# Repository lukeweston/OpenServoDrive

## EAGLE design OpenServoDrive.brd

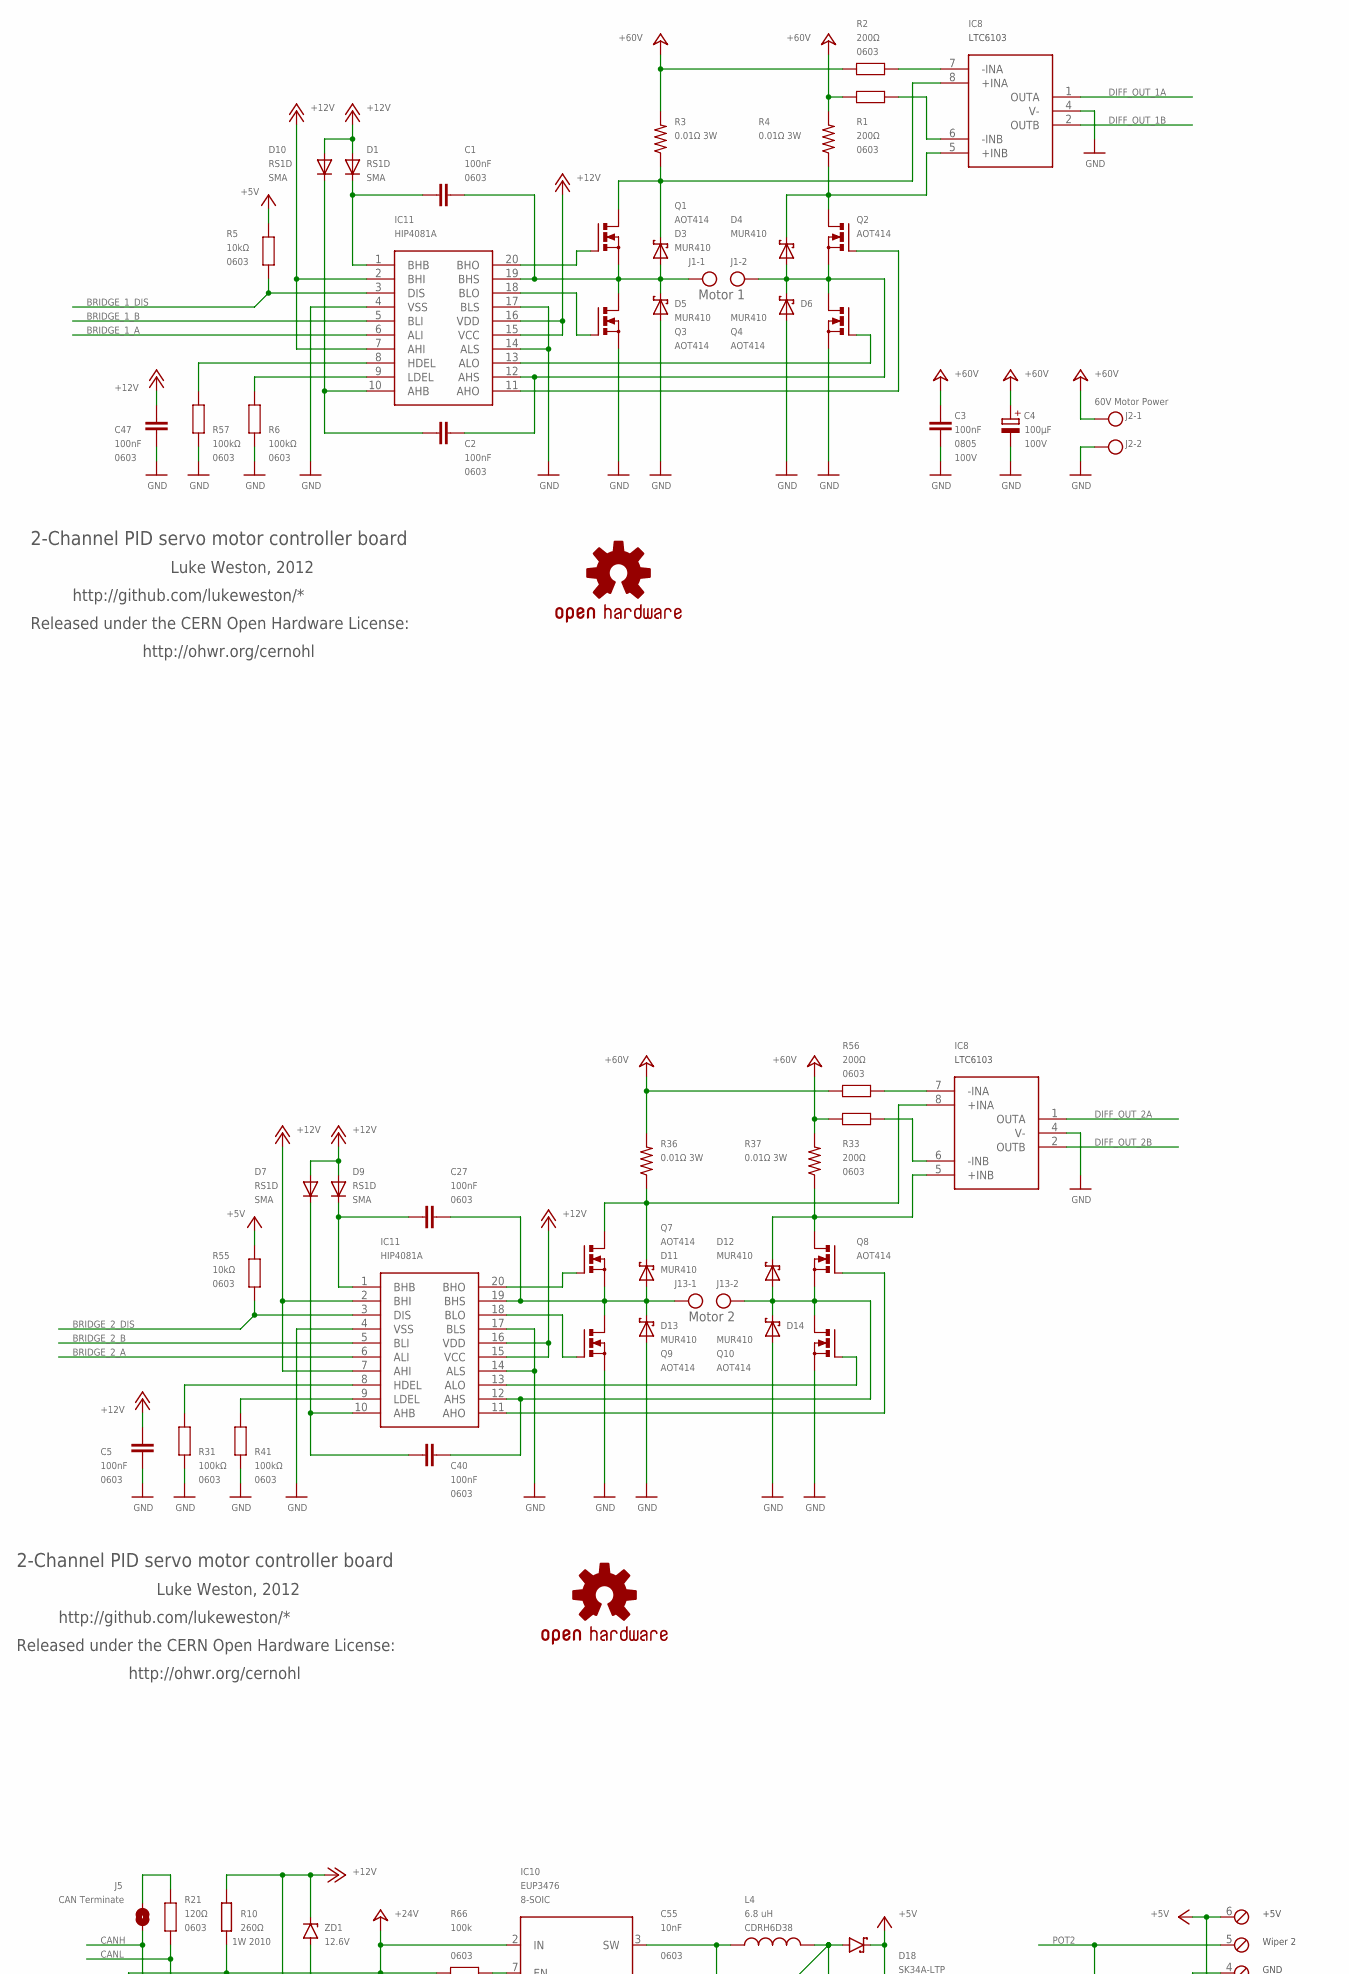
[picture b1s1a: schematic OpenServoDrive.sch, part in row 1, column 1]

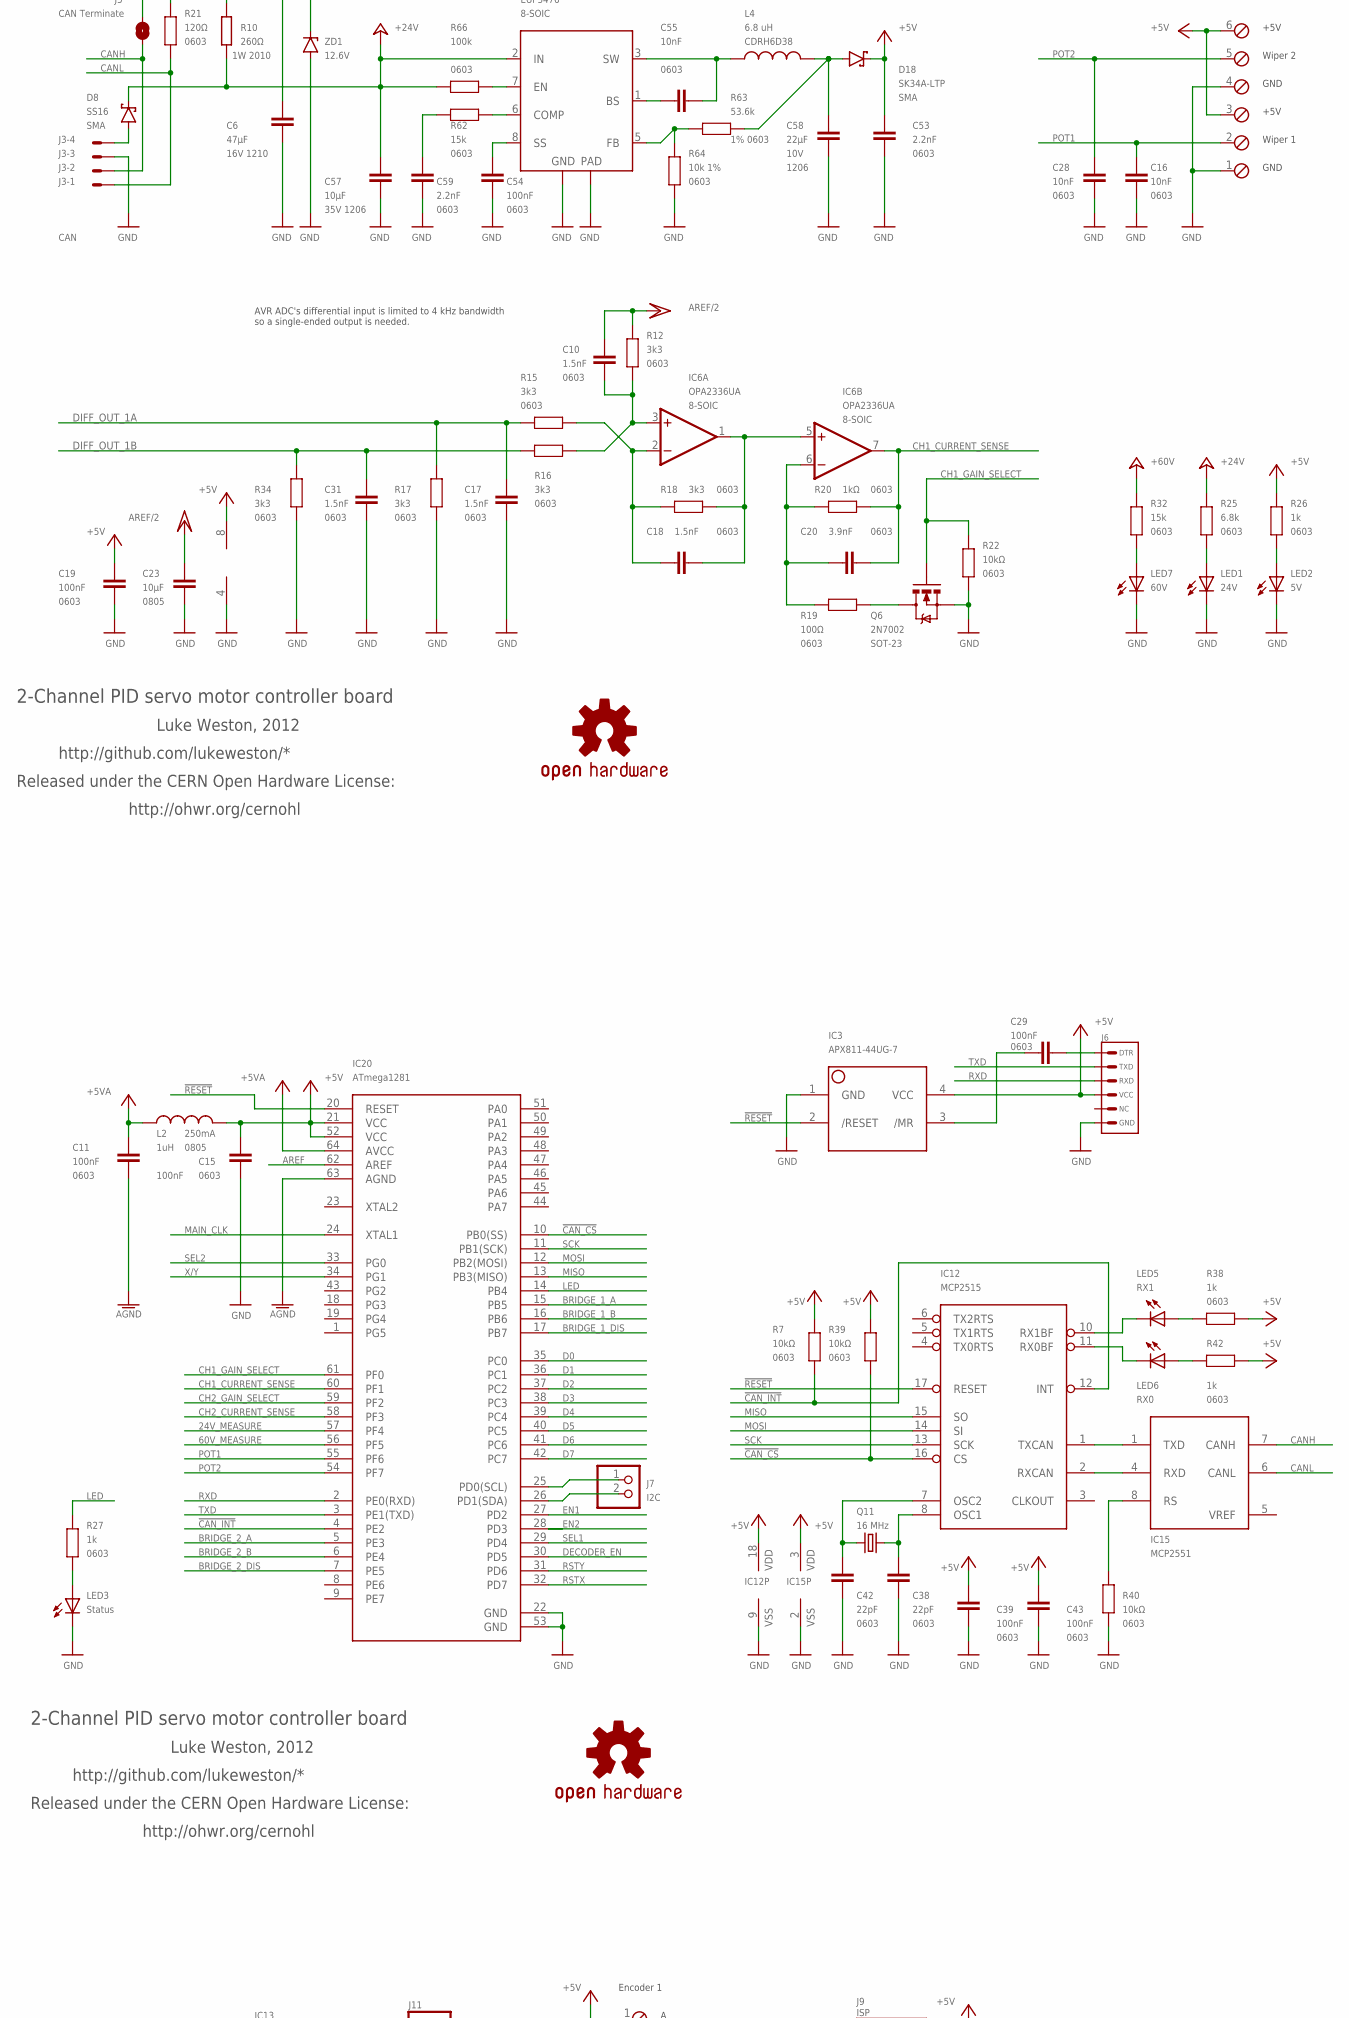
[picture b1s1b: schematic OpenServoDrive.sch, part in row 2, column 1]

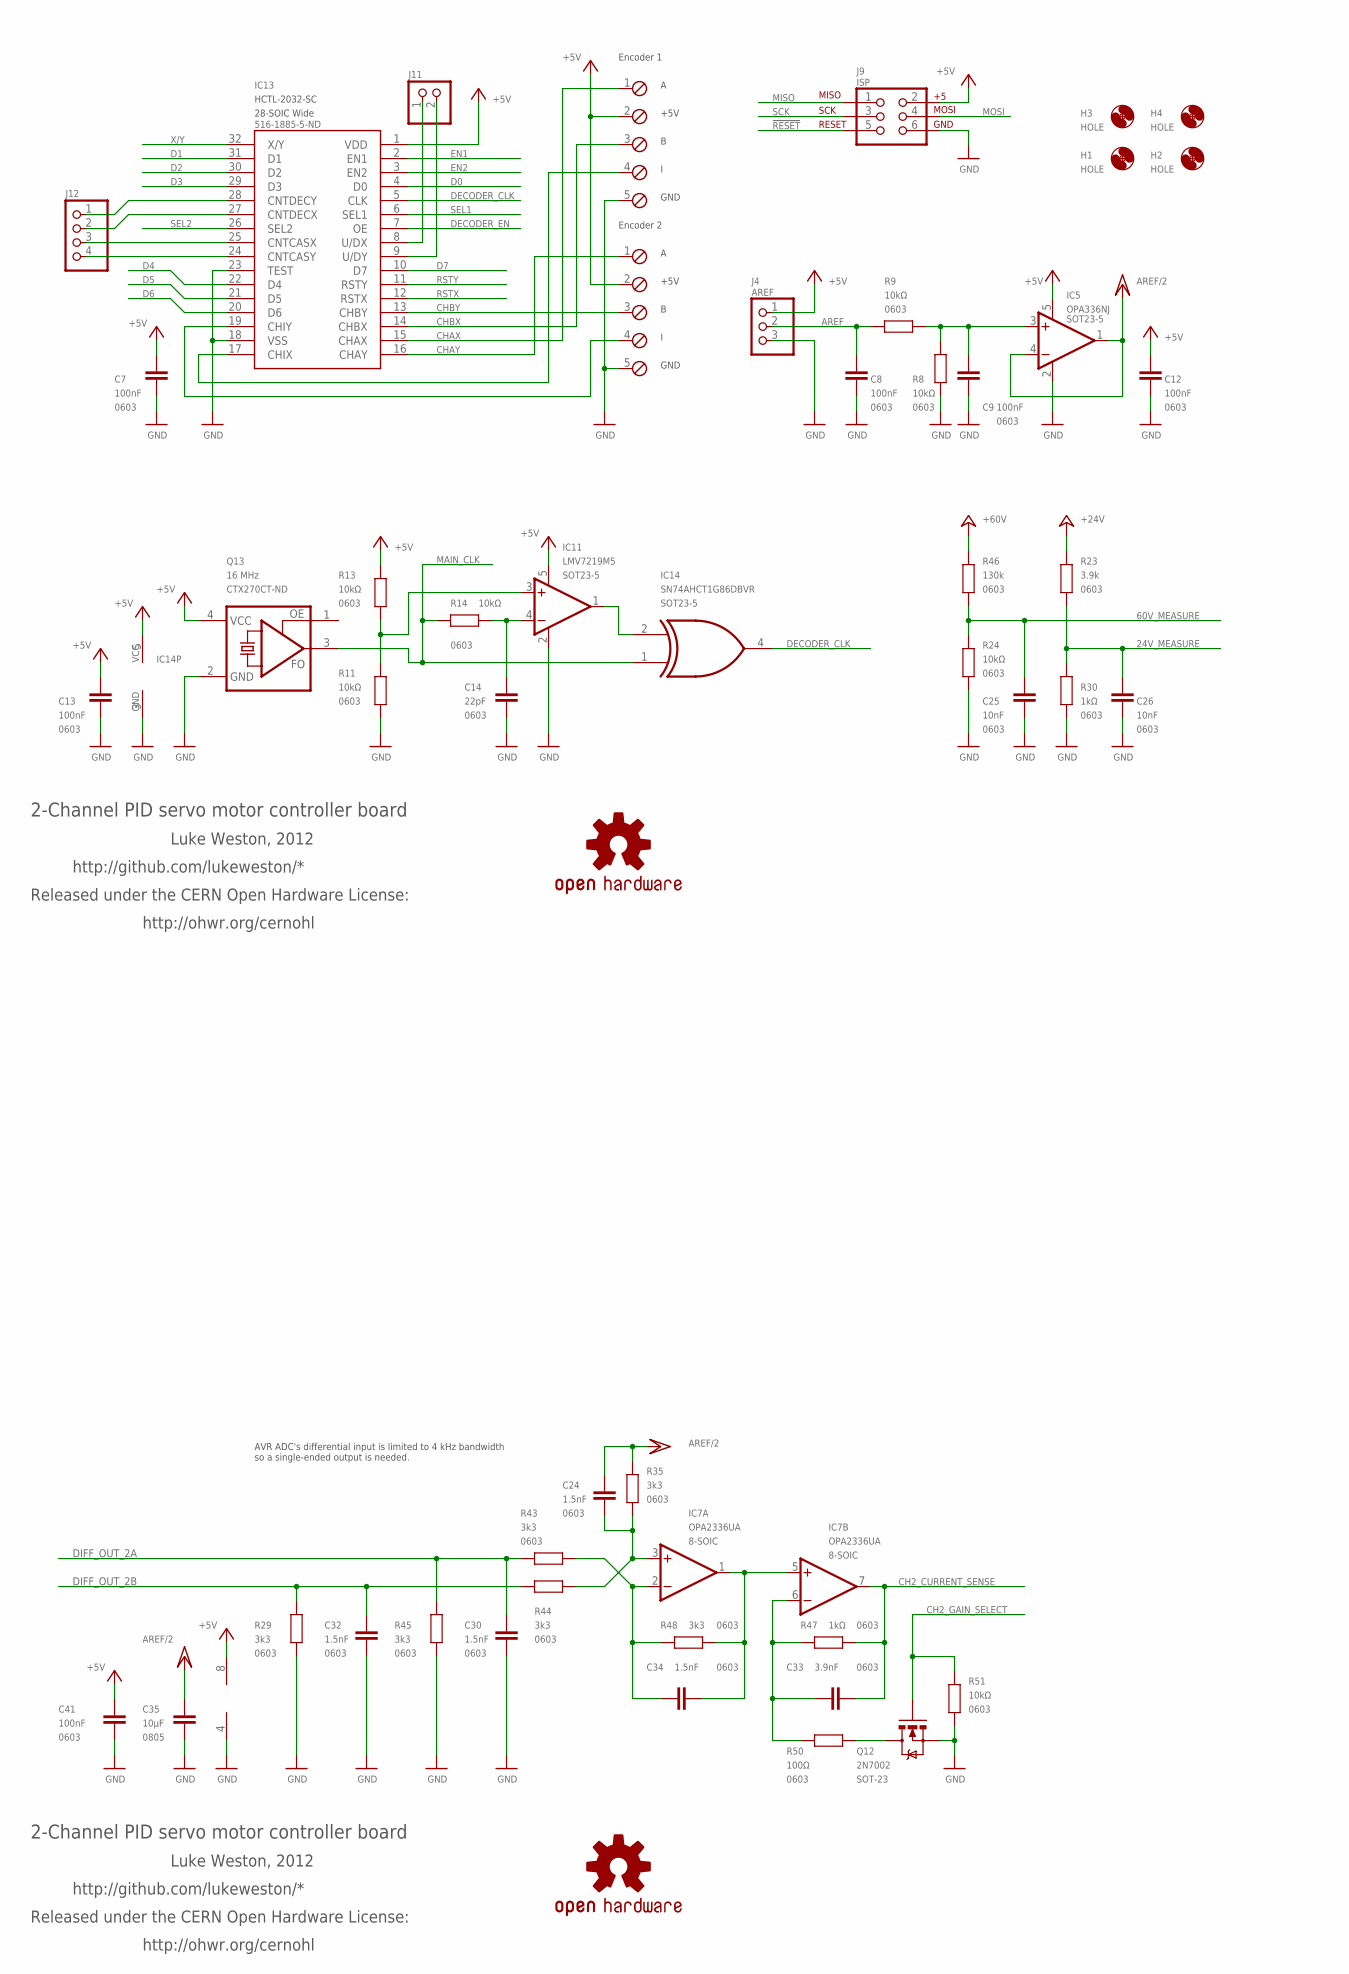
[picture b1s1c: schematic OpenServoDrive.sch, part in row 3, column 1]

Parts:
C1, C2, C5, C7, C8, C9, C11, C12, C13, C15, C19, C27, C29, C39, C40, C41, C43, C47, C54: 100nF; 0603
C3: 100nF; 0805; VOLTAGE 100V
C4: 100µF; E5-10,5; VOLTAGE 100V
C6: 47µF; C1210; VOLTAGE 16V 1210
C10, C17, C18, C24, C30, C31, C32, C34: 1.5nF; 0603
C14, C38, C42: 22pF; 0603
C16, C25, C26, C28, C55: 10nF; 0603
C20, C33: 3.9nF; 0603
C23, C35: 10µF; 0805
C53, C59: 2.2nF; 0603
C57: 10µF; C1206K; VOLTAGE 35V 1206
C58: 22µF; C1206K; VOLTAGE 10V
D1, D7, D9, D10: RS1D; SMA-DIODE
D3, D4, D5, D6, D11, D12, D13, D14: MUR410; DO201T15
D8: SS16; SMA
D18: SK34A-LTP; SMA
H1, H2, H3, H4: HOLE; 3,2
IC1, IC9: LTC6103; SO08
IC2, IC16: HIP4081A; SO20W
IC3: APX811-44UG-7; SOT143-R
IC5: OPA336NJ; SOT23-5
IC6, IC7: OPA2336UA; SO08
IC10: EUP3476; SO08T
IC11: LMV7219M5; SOT23-5
IC12: MCP2515; SO-18W
IC13: HCTL-2032-SC; SO28W
IC14: SN74AHCT1G86DBVR; SOT23-5
IC15: MCP2551; SO-08
IC20: ATmega1281; TQFP64_14X14MM
J1: Motor 1; W237-102
J2: 60V Motor Power; W237-102
J3: CAN; 7395-04
J4: AREF; 1X03
J5: CAN Terminate; SJ
J6: ARDUINO_SERIAL_PROGRAMLONGPADS; 1X06_LONGPADS
J7: I2C; 1X02
J9: ISP; 2X3
J11: PINHD-1X2; 1X02
J12: PINHD-1X4; 1X04
J13: Motor 2; W237-102
L2: 1uH; L2012C
L4: 6.8 uH; CDRH
LED1: 24V; LED-0603
LED2: 5V; LED-0603
LED3: Status; LED-0603
LED5: RX1; LED-0603
LED6: RX0; LED-0603
LED7: 60V; LED-0603
Q1, Q2, Q3, Q4, Q7, Q8, Q9, Q10: AOT414; TO220BH
Q6, Q12: 2N7002; SOT23-3
Q11: 16 MHz; HC49US
Q13: 16 MHz; ASF
R1, R2, R33, R56: 200Ω; 0603
R3, R4, R36, R37: 0.01Ω 3W; RSENSE
R5, R7, R8, R9, R11, R13, R14, R22, R24, R39, R40, R51, R55: 10kΩ; 0603
R6, R31, R41, R57: 100kΩ; 0603
R10: 260Ω; R2010
R12, R15, R16, R17, R18, R29, R34, R35, R43, R44, R45, R48: 3k3; 0603
R19, R50: 100Ω; 0603
R20, R30, R47: 1kΩ; 0603
R21: 120Ω; 0603
R23: 3.9k; 0603
R25: 6.8k; 0603
R26, R27, R38, R42: 1k; 0603
R32, R62: 15k; 0603
R46: 130k; 0603
R63: 53.6k; 0603
R64: 10k 1%; 0603
R66: 100k; 0603
U$1, U$2, U$5, U$55, U$56, U$68: OSHW-LOGOS; OSHW-LOGO-S
X1: MPT6; 6POL254
X2, X3: MPT5; 5POL254
ZD1: 12.6V; MINIMELF

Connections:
24V_MEASURE: C26.2, IC20.57 (PF4), R23.1, R30.1
60V_MEASURE: C25.2, IC20.56 (PF5), R24.1, R46.1
!CAN_CS: IC12.16 (CS), IC20.10 (PB0(SS)), R39.2
!CAN_INT: IC12.12 (INT), IC20.4 (PE2), R7.2
!RESET: IC3.2 (/RESET), IC12.17 (RESET), IC20.20 (RESET), J9.5
+5V: C7.2, C12.2, C13.2, C15.1, C19.1, C39.2, C41.1, C43.2, C53.2, D18.K, IC3.4 (VCC), IC5.5 (V+), IC6.8 (V+), IC7.8 (V+), IC11.5 (V+), IC12.18 (VDD), IC13.1 (VDD), IC14.5 (VCC), IC15.3 (VDD), IC20.21 (VCC), IC20.52 (VCC), IC20.64 (AVCC), J4.1, J6.4 (VCC), J9.2, L2.2, Q13.4 (VCC), R5.2, R7.1, R13.1, R26.1, R38.2, R39.1, R42.2, R55.2, X1.3, X1.6, X2.2, X3.2
+5VA: C11.1, L2.1
+12V: C5.1, C6.1, C47.1, D1.A, D7.A, D9.A, D10.A, IC2.2 (BHI), IC2.7 (AHI), IC2.15 (VCC), IC2.16 (VDD), IC16.2 (BHI), IC16.7 (AHI), IC16.15 (VCC), IC16.16 (VDD), R10.2, ZD1.K
+24V: C57.1, D8.K, IC10.2 (IN), R10.1, R23.2, R25.1, R66.2
+60V: C3.2, C4.+, J2.1, R1.2, R2.2, R3.P$2 (2), R4.P$2 (2), R32.1, R33.2, R36.P$2 (2), R37.P$2 (2), R46.2, R56.2
AGND: C11.2, IC20.63 (AGND)
AREF: C8.2, IC20.62 (AREF), J4.2, R9.1
AREF/2: C10.1, C23.1, C24.1, C35.1, IC5.1 (OUT), IC5.4 (-IN), R12.2, R35.2
BRIDGE_1_A: IC2.6 (ALI), IC20.15 (PB5)
BRIDGE_1_B: IC2.5 (BLI), IC20.16 (PB6)
BRIDGE_1_DIS: IC2.3 (DIS), IC20.17 (PB7), R5.1
BRIDGE_2_A: IC16.6 (ALI), IC20.5 (PE3)
BRIDGE_2_B: IC16.5 (BLI), IC20.6 (PE4)
BRIDGE_2_DIS: IC16.3 (DIS), IC20.7 (PE5), R55.1
CANH: IC15.7 (CANH), J3.2, J5.2
CANL: IC15.6 (CANL), J3.1, R21.1
CH1_CURRENT_SENSE: C20.2, IC6.7 (OUT), IC20.60 (PF1), R20.1
CH1_GAIN_SELECT: IC20.61 (PF0), Q6.1 (G), R22.2
CH2_CURRENT_SENSE: C33.2, IC7.7 (OUT), IC20.58 (PF3), R47.1
CH2_GAIN_SELECT: IC20.59 (PF2), Q12.1 (G), R51.2
CHAX: IC13.15 (CHAX), X2.1
CHAY: IC13.16 (CHAY), X3.1
CHBX: IC13.14 (CHBX), X2.3
CHBY: IC13.13 (CHBY), X3.3
CHIX: IC13.17 (CHIX), X2.4
CHIY: IC13.19 (CHIY), X3.4
D0: IC13.4 (D0), IC20.35 (PC0)
D1: IC13.31 (D1), IC20.36 (PC1)
D2: IC13.30 (D2), IC20.37 (PC2)
D3: IC13.29 (D3), IC20.38 (PC3)
D4: IC13.22 (D4), IC20.39 (PC4)
D5: IC13.21 (D5), IC20.40 (PC5)
D6: IC13.20 (D6), IC20.41 (PC6)
D7: IC13.10 (D7), IC20.42 (PC7)
DECODER_CLK: IC13.5 (CLK), IC14.4 (O)
DECODER_EN: IC13.7 (OE), IC20.30 (PD5)
DIFF_OUT_1A: C17.1, IC1.1 (OUTA), R15.2, R17.2
DIFF_OUT_1B: C31.1, IC1.2 (OUTB), R16.2, R34.2
DIFF_OUT_2A: C30.1, IC9.1 (OUTA), R43.2, R45.2
DIFF_OUT_2B: C32.1, IC9.2 (OUTB), R29.2, R44.2
EN1: IC13.2 (EN1), IC20.27 (PD2)
EN2: IC13.3 (EN2), IC20.28 (PD3)
GND: C3.1, C4.-, C5.2, C6.2, C7.1, C8.1, C9.1, C12.1, C13.1, C14.1, C15.2, C16.2, C17.2, C19.2, C23.2, C25.1, C26.1, C28.2, C30.2, C31.2, C32.2, C35.2, C38.1, C39.1, C41.2, C42.1, C43.1, C47.2, C53.1, C54.1, C57.2, C58.2, C59.1, D5.A, D6.A, D13.A, D14.A, IC1.4 (V-), IC2.4 (VSS), IC2.14 (ALS), IC2.17 (BLS), IC3.1 (GND), IC5.2 (V-), IC6.4 (V-), IC7.4 (V-), IC9.4 (V-), IC10.4 (GND), IC10.9 (TGND), IC11.2 (V-), IC12.9 (VSS), IC13.18 (VSS), IC13.23 (TEST), IC14.3 (GND), IC15.2 (VSS), IC16.4 (VSS), IC16.14 (ALS), IC16.17 (BLS), IC20.22 (GND), IC20.53 (GND), J2.2, J3.3, J4.3, J6.6 (GND), J9.6, LED1.C, LED2.C, LED3.C, LED7.C, Q3.S, Q4.S, Q6.2 (S), Q9.S, Q10.S, Q12.2 (S), Q13.2 (GND), R6.1, R8.2, R11.2, R17.1, R22.1, R24.2, R29.1, R30.2, R31.1, R34.1, R40.2, R41.1, R45.1, R51.1, R57.1, R64.2, X1.1, X1.4, X2.5, X3.5, ZD1.A
LED: IC20.14 (PB4), R27.1
MAIN_CLK: IC14.1 (I0), IC20.24 (XTAL1), Q13.3 (FO), R14.1
MISO: IC12.15 (SO), IC20.13 (PB3(MISO)), J9.1
MOSI: IC12.14 (SI), IC20.12 (PB2(MOSI)), J9.4
unnamed: IC13.28 (CNTDECY), J12.1
unnamed: C34.1, IC7.2 (-IN), R43.1, R48.2
unnamed: C14.2, IC11.4 (-IN), R14.2
unnamed: IC11.1 (OUT), IC14.2 (I1)
unnamed: IC11.3 (+IN), R11.1, R13.2
unnamed: IC1.7 (-INA), R2.1
unnamed: IC13.25 (CNTCASX), J12.3
unnamed: IC13.24 (CNTCASY), J12.4
unnamed: IC13.27 (CNTDECX), J12.2
unnamed: IC13.8 (U/DX), J11.1
unnamed: C24.2, IC7.3 (+IN), R35.1, R44.1
unnamed: IC13.9 (U/DY), J11.2
unnamed: LED2.A, R26.2
unnamed: C9.2, IC5.3 (+IN), R8.1, R9.2
unnamed: IC1.6 (-INB), R1.1
unnamed: C33.1, IC7.6 (-IN), R47.2, R50.2
unnamed: Q12.3 (D), R50.1
unnamed: C34.2, IC7.1 (OUT), IC7.5 (+IN), R48.1
unnamed: IC20.26 (PD1(SDA)), J7.2
unnamed: IC20.25 (PD0(SCL)), J7.1
unnamed: C18.1, IC6.2 (-IN), R15.1, R18.2
unnamed: C29.2, IC3.3 (/MR)
unnamed: C29.1, J6.1 (DTR)
unnamed: C10.2, IC6.3 (+IN), R12.1, R16.1
unnamed: D8.A, J3.4
unnamed: J5.1, R21.2
unnamed: C20.1, IC6.6 (-IN), R19.2, R20.2
unnamed: Q6.3 (D), R19.1
unnamed: C2.2, D4.A, D6.C, IC2.12 (AHS), J1.2, Q2.S, Q4.D
unnamed: C18.2, IC6.1 (OUT), IC6.5 (+IN), R18.1
unnamed: D4.C, IC1.5 (+INB), Q2.D, R4.P$1 (1)
unnamed: C1.2, D3.A, D5.C, IC2.19 (BHS), J1.1, Q1.S, Q3.D
unnamed: IC10.7 (EN), R66.1
unnamed: LED1.A, R25.2
unnamed: C55.1, IC10.3 (SW), L4.1
unnamed: D3.C, IC1.8 (+INA), Q1.D, R3.P$1 (1)
unnamed: IC2.20 (BHO), Q1.G
unnamed: IC2.18 (BLO), Q3.G
unnamed: IC2.13 (ALO), Q4.G
unnamed: IC2.11 (AHO), Q2.G
unnamed: LED3.A, R27.2
unnamed: C55.2, IC10.1 (BS)
unnamed: IC12.1 (TXCAN), IC15.1 (TXD)
unnamed: IC12.2 (RXCAN), IC15.4 (RXD)
unnamed: LED7.A, R32.2
unnamed: C38.2, IC12.8 (OSC1), Q11.2
unnamed: C42.2, IC12.7 (OSC2), Q11.1
unnamed: IC12.11 (RX0BF), LED6.C
unnamed: C59.2, R62.2
unnamed: C2.1, D10.C, IC2.10 (AHB)
unnamed: IC10.6 (COMP), R62.1
unnamed: C54.2, IC10.8 (SS)
unnamed: IC10.5 (FB), R63.2, R64.1
unnamed: C58.1, D18.A, L4.2, R63.1
unnamed: C1.1, D1.C, IC2.1 (BHB)
unnamed: C40.2, D12.A, D14.C, IC16.12 (AHS), J13.2, Q8.S, Q10.D
unnamed: D12.C, IC9.5 (+INB), Q8.D, R37.P$1 (1)
unnamed: C27.2, D11.A, D13.C, IC16.19 (BHS), J13.1, Q7.S, Q9.D
unnamed: IC2.9 (LDEL), R6.2
unnamed: IC2.8 (HDEL), R57.2
unnamed: D11.C, IC9.8 (+INA), Q7.D, R36.P$1 (1)
unnamed: IC16.20 (BHO), Q7.G
unnamed: IC16.18 (BLO), Q9.G
unnamed: IC16.13 (ALO), Q10.G
unnamed: IC12.10 (RX1BF), LED5.C
unnamed: LED6.A, R42.1
unnamed: LED5.A, R38.1
unnamed: IC15.8 (RS), R40.1
unnamed: IC16.11 (AHO), Q8.G
unnamed: C40.1, D7.C, IC16.10 (AHB)
unnamed: C27.1, D9.C, IC16.1 (BHB)
unnamed: IC16.9 (LDEL), R41.2
unnamed: IC16.8 (HDEL), R31.2
unnamed: IC9.7 (-INA), R56.1
unnamed: IC9.6 (-INB), R33.1
POT1: C16.1, IC20.55 (PF6), X1.2
POT2: C28.1, IC20.54 (PF7), X1.5
RSTX: IC13.12 (RSTX), IC20.32 (PD7)
RSTY: IC13.11 (RSTY), IC20.31 (PD6)
RXD: IC20.2 (PE0(RXD)), J6.3 (TXO)
SCK: IC12.13 (SCK), IC20.11 (PB1(SCK)), J9.3
SEL1: IC13.6 (SEL1), IC20.29 (PD4)
SEL2: IC13.26 (SEL2), IC20.33 (PG0)
TXD: IC20.3 (PE1(TXD)), J6.2 (RXI)
VREF: IC15.5 (VREF)
X/Y: IC13.32 (X/Y), IC20.34 (PG1)

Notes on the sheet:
516-1885-5-ND
HCTL-2032-SC
Encoder 1
Encoder 2
+5V
GND
HIP4081A
LTC6103
Wiper 2
Wiper 1
AVR ADC's differential input is limited to 4 kHz bandwidth so a single-ended output is needed.
IC11
IC8
2-Channel PID servo motor controller board
Luke Weston, 2012
http://github.com/lukeweston/*
Released under the CERN Open Hardware License:
http://ohwr.org/cernohl
28-SOIC Wide

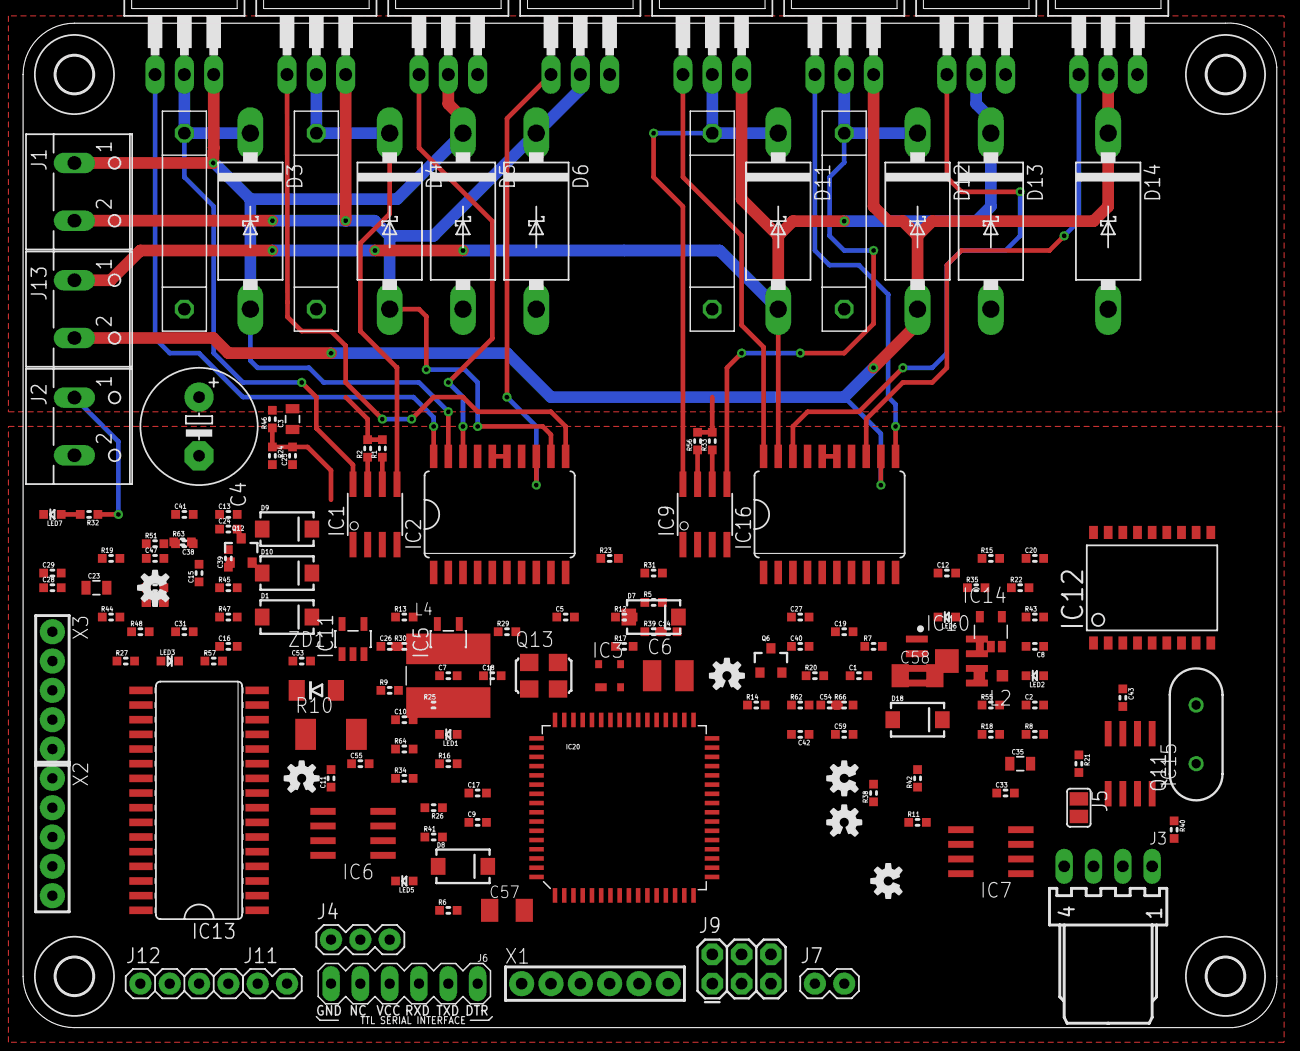
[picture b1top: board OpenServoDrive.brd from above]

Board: 2 copper layers, 108.6 x 87.0 mm, 176 parts (0 on the bottom side), 137 nets.
